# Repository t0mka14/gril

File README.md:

# gril
A gril control unit for reflowing pcbs. The project consists of two parts - Micropython code for Rpi Pico and one PCB. \
**PCB**\
Apart from the Pico there is MAX31855 that converts temperature of thermocouple glued to the grill plate and sends it over SPI to PICO. Then there is one mosfet to control external SSR and linear stabilizer as the input voltage is 12V. The whole device is controlled using rotary encoder connected to GPIO pins 19-21. The encoder button goes to 19. The display is any 16x4 I2C LCD.\
**Code**\
The code uses two Asyncio loops, one for controlling temperature and on for displaying stuff. If you want to tune the PID controller, you can change parameters on line 92 in gril.py

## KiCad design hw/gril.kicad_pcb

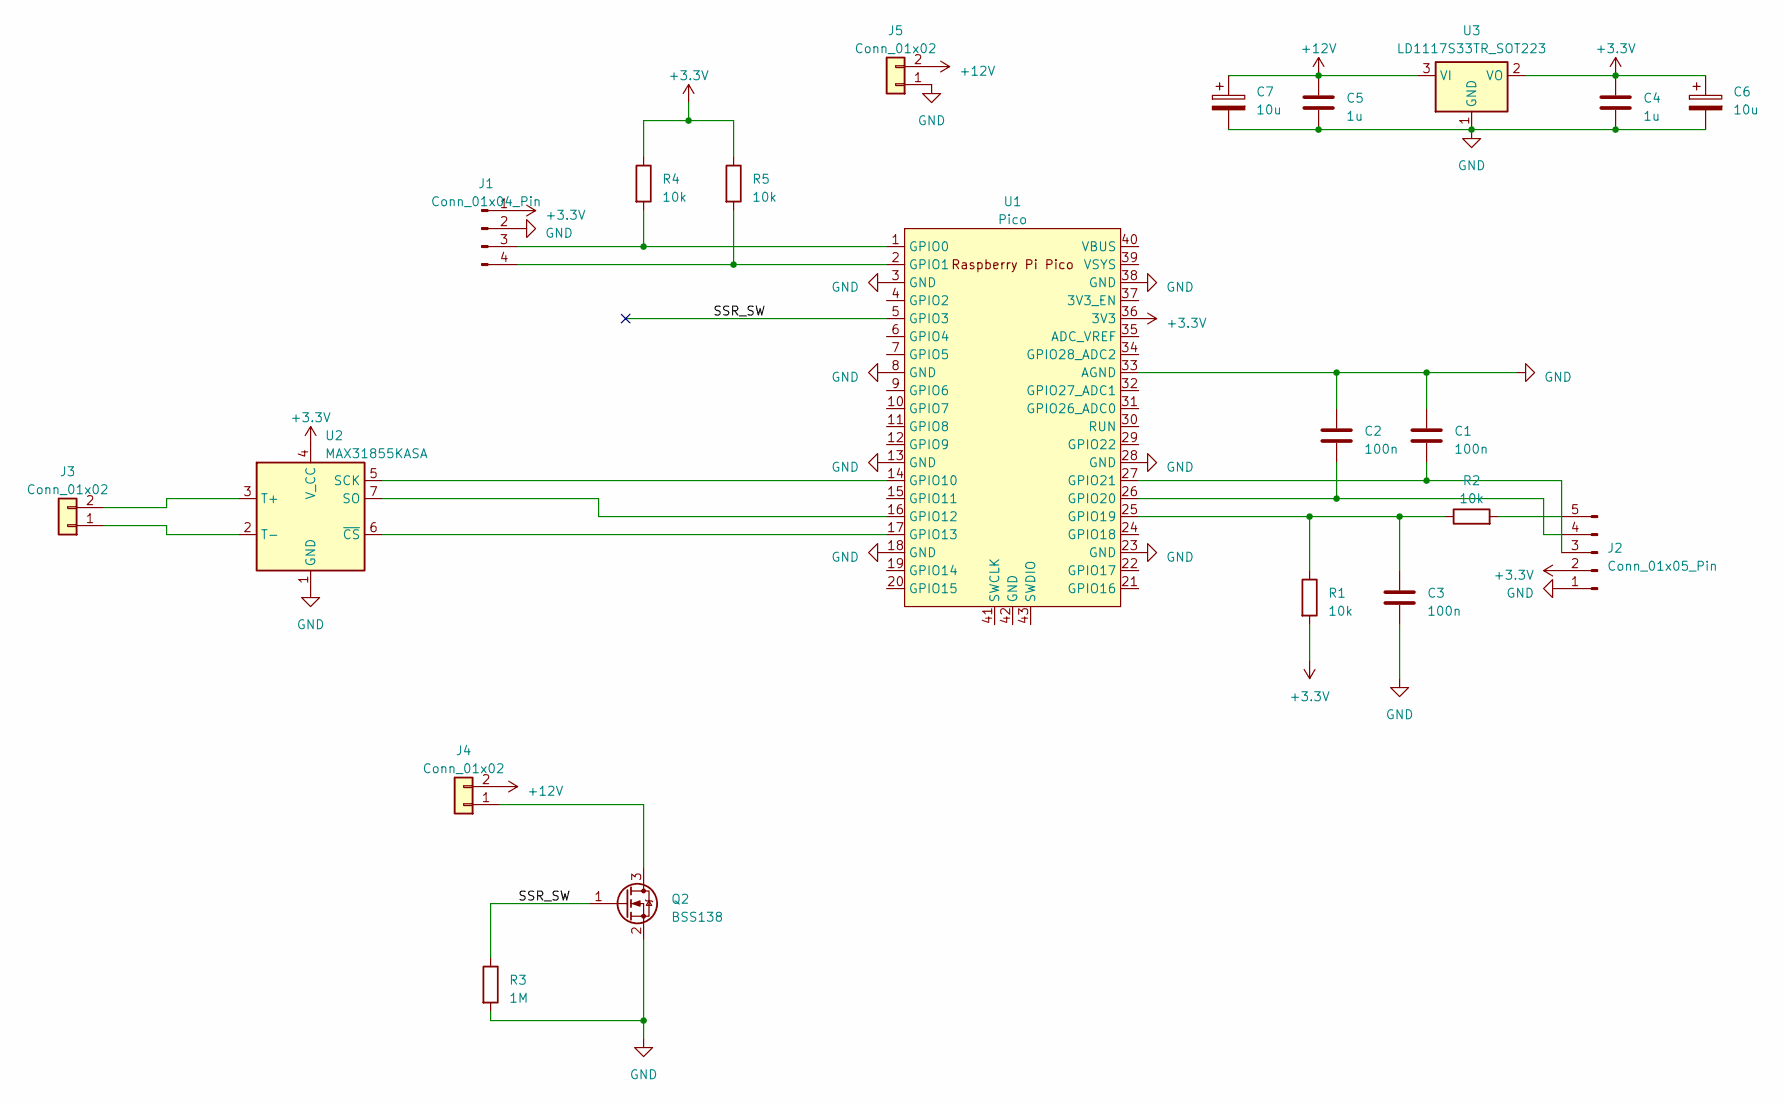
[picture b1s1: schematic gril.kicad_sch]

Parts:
C1: 100n; NetTie-4_SMD_Pad0.5mm
C2, C3: 100n; C_0805_2012Metric
C4, C5: 1u; C_0805_2012Metric
C6, C7: 10u; CP_Radial_D8.0mm_P3.80mm
J1: Conn_01x04_Pin; PinHeader_1x04_P2.54mm_Vertical
J2: Conn_01x05_Pin; PinHeader_1x05_P2.54mm_Vertical
J3, J4, J5: Conn_01x02; PinHeader_1x02_P2.54mm_Vertical
Q2: BSS138; SOT-23
R1, R2, R4, R5: 10k; R_0805_2012Metric
R3: 1M; R_0805_2012Metric
U1: Pico; RPi_Pico_SMD_TH
U2: MAX31855KASA; SOIC-8_3.9x4.9mm_P1.27mm
U3: LD1117S33TR_SOT223; SOT-223-3_TabPin2

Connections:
+3.3V: C4.1, C6.1, J1.1, J2.2, R1.2, R4.1, R5.1, U1.36 (3V3), U2.4 (V_CC), U3.2 (VO)
+12V: C5.1, C7.1, J4.2, J5.2, U3.3 (VI)
/SSR_SW: Q2.1 (G), R3.1, U1.5 (GPIO3)
GND: C1.2, C2.1, C3.2, C4.2, C5.2, C6.2, C7.2, J1.2, J2.1, J5.1, Q2.2 (S), R3.2, U1.3 (GND), U1.8 (GND), U1.13 (GND), U1.18 (GND), U1.23 (GND), U1.28 (GND), U1.33 (AGND), U1.38 (GND), U2.1 (GND), U3.1 (GND)
unnamed: J1.3, R4.2, U1.1 (GPIO0)
unnamed: J1.4, R5.2, U1.2 (GPIO1)
unnamed: C1.1, J2.3, U1.27 (GPIO21)
unnamed: C2.2, J2.4, U1.26 (GPIO20)
unnamed: J2.5, R2.2
unnamed: J3.1, U2.2 (T-)
unnamed: J3.2, U2.3 (T+)
unnamed: J4.1, Q2.3 (D)
unnamed: U1.14 (GPIO10), U2.5 (SCK)
unnamed: U1.16 (GPIO12), U2.7 (SO)
unnamed: U1.17 (GPIO13), U2.6 (~CS)
unnamed: C3.1, R1.1, R2.1, U1.25 (GPIO19)

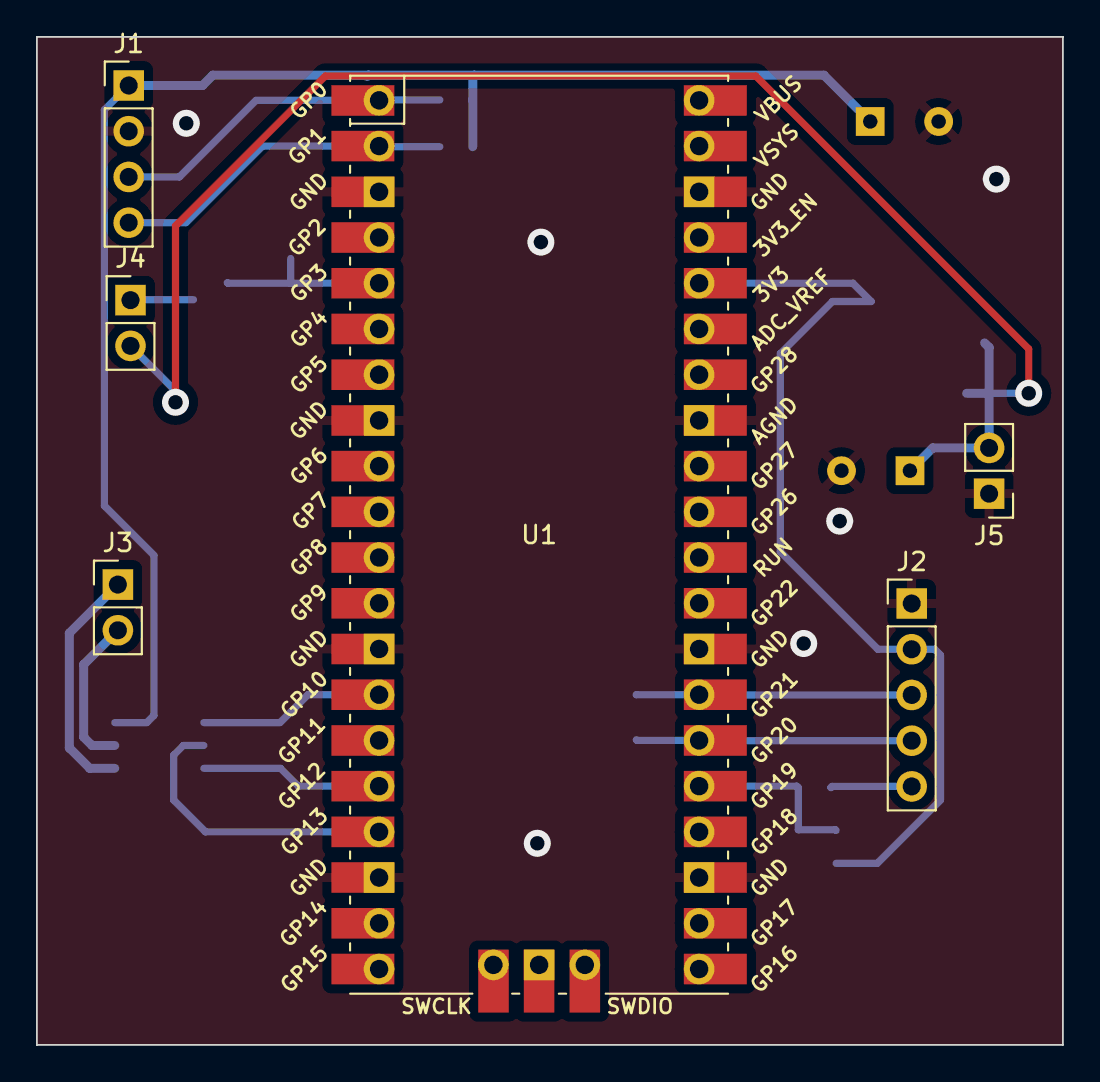
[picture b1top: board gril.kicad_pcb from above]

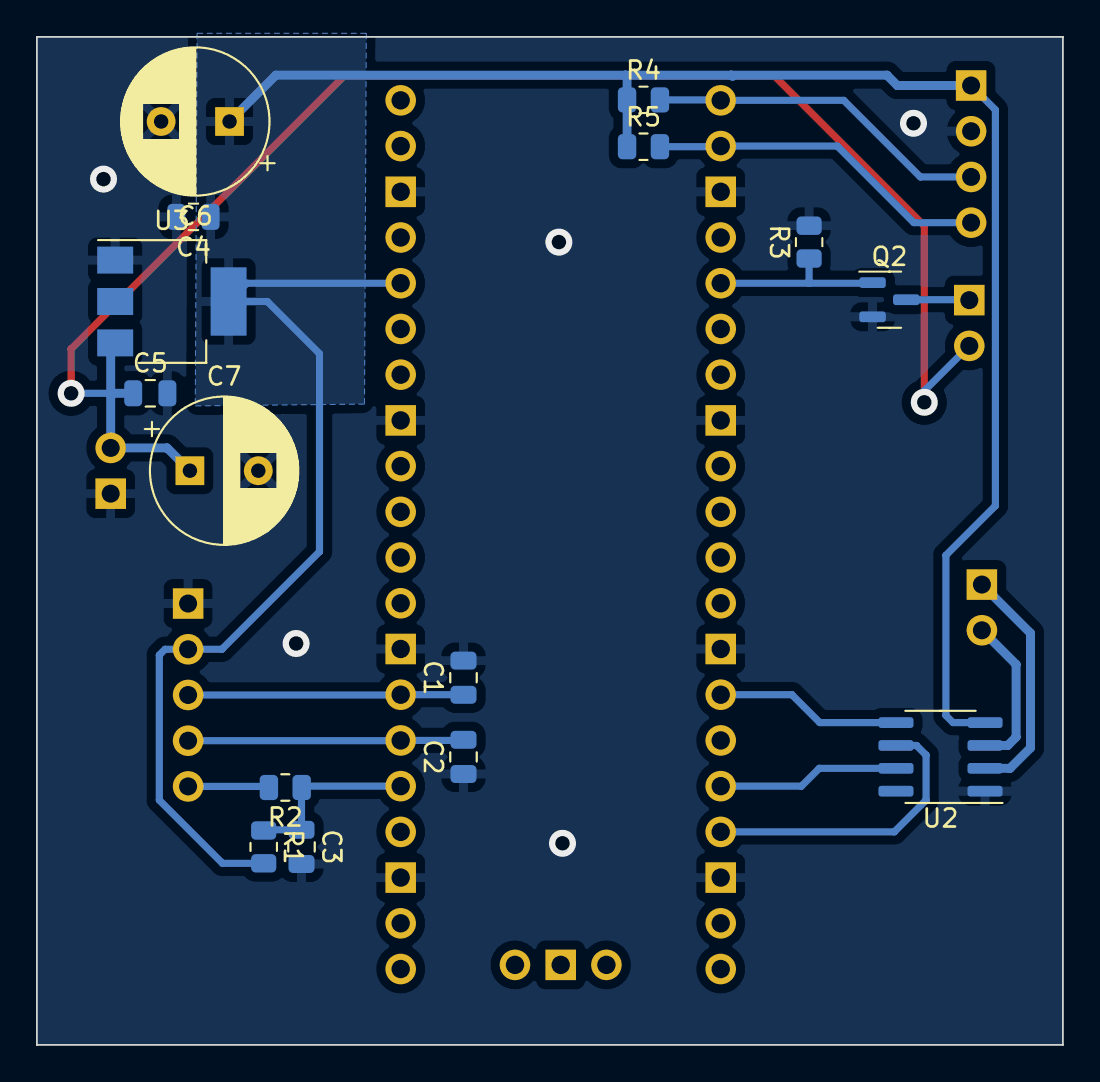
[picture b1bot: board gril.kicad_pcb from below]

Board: 2 copper layers, 57.0 x 56.0 mm, 21 parts (15 on the bottom side), 16 nets.

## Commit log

2025-03-21 init commit
